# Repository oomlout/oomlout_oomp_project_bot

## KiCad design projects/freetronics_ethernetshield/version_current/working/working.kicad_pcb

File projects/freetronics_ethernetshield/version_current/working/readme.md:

# OOMP Project  
## EthernetShield  by freetronics  
  
oomp key: oomp_projects_flat_freetronics_ethernetshield  
(snippet of original readme)  
  
Freetronics Ethernet Shield  
===========================  
Copyright 2010-2012 Freetronics Pty Ltd    
Freetronics site:  www.freetronics.com    
Freetronics email: info@freetronics.com    
  
10/100base-T Ethernet shield for the Freetronics Eleven, Arduino Uno,  
and other boards compatible with the R3 header format.  
  
Includes significant prototyping area using the spare shield area, and  
supports Power-over-Ethernet (PoE) using either simple jumpers for DIY  
PoE or a daughter-board module for full standards-compliant PoE.  
  
Features:  
  
 * Prototyping area.  
 * 10/100Base-T connectivity.  
 * Power-over-Ethernet "PD" (powered device) support.  
 * Activity / status indicators.  
 * Reset button wired through to Arduino reset pin.  
 * Wiznet W5100 IC reset circuit.  
 * SPI bus contention fixed for W5100 IC.  
 * Parts overlay on both the top and the bottom.  

More information is available on our product page at:  
  
  http://www.freetronics.com/ethernet  
  
The "docs" folder within this repository includes a handy copy of the  
schematic in PDF format and image(s) of the pcb.  

INSTALLATION  
------------  
The design is saved as an EAGLE project. EAGLE PCB design software is  
available from www.cadsoftusa.com free for non-commercial use. To use  
this project download it and place the directory containing these files  
into the "eagle" directory on your computer. Then open EAGLE and  
navigate to Projects -> eagle -> EthernetShieldR3.  

DISTRIBUTION  
------------  
The specific terms of distribution of this project are gove  
  full source readme at [readme_src.md](readme_src.md)  
  
source repo at: [https://github.com/freetronics/EthernetShield](https://github.com/freetronics/EthernetShield)  
## Board  

## Schematic  

[schematic pdf](working_schematic.pdf)  
## Images

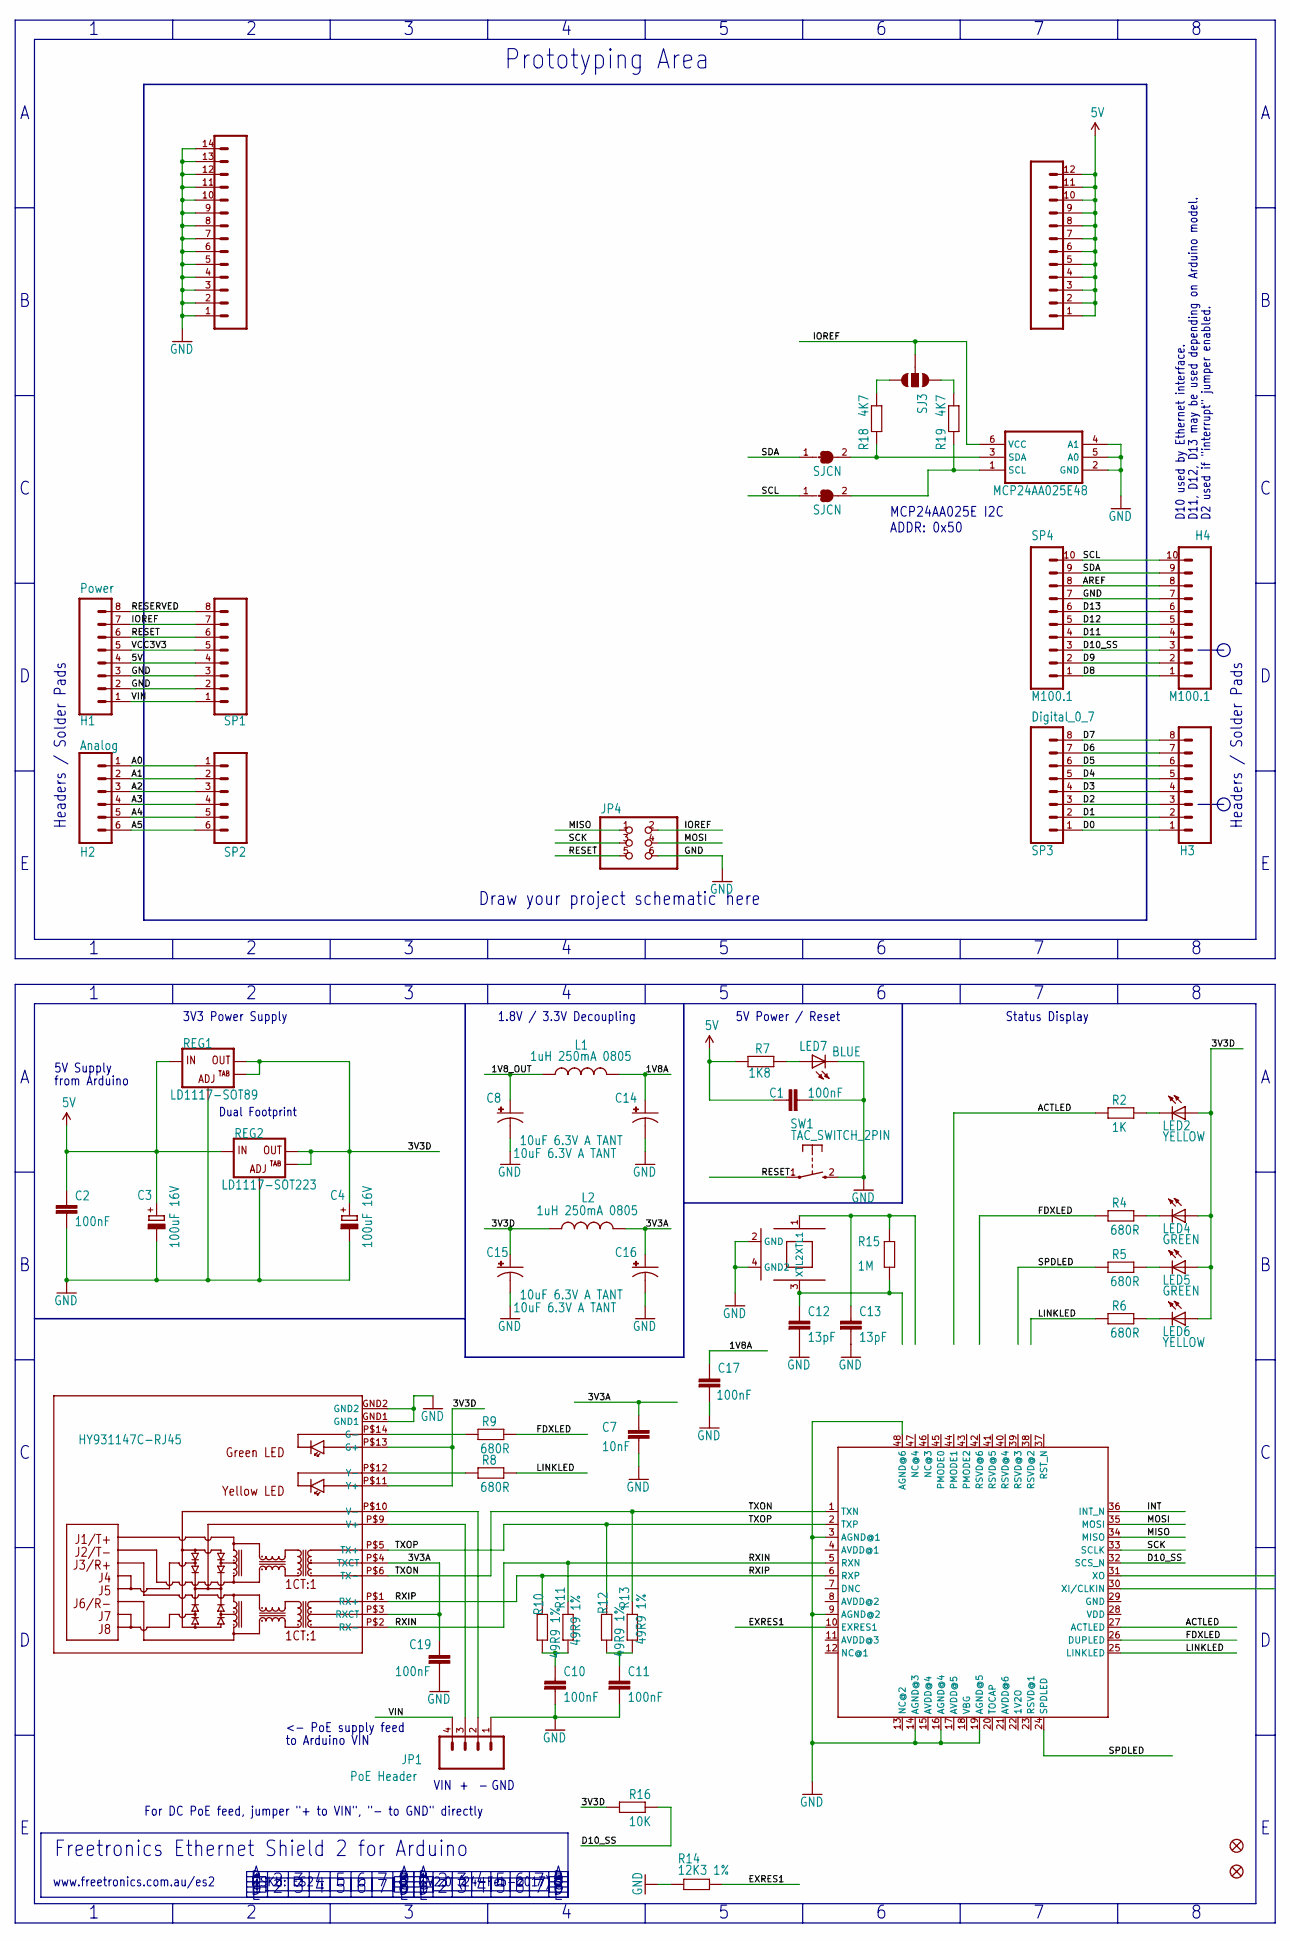
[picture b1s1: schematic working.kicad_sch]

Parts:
C1, C2, C10, C11, C17, C19: 100nF; 0603
C3, C4: 100uF 16V; PANASONIC_D
C7: 10nF; 0603
C8, C14, C15, C16: 10uF 6.3V A TANT; EIA3216
C12, C13: 13pF; 0603
H1: Power; 1X08
H2: Analog; 1X06
H3: Digital_0_7; 1X08
H4: M100.1; 1X10
IC1: W5500
IC2: MCP24AA025E48; SOT23-6
JP1: PoE Header; 1X04
JP4: PINHD-2X3; 2X03
L1, L2: 1uH 250mA 0805; L2012C
LED2, LED6: YELLOW; LED-0603
LED4, LED5: GREEN; LED-0603
LED7: BLUE; LED-0603
PADS_5V0: M12PTH; 1X12
PADS_GND0: M14; 1X14
R2: 1K; 0603
R4, R5, R6, R8, R9: 680R; 0603
R7: 1K8; 0603
R10, R11, R12, R13: 49R9 1%; 0603
R14: 12K3 1%; 0603
R15: 1M; 0603
R16: 10K; 0603
R18, R19: 4K7; 0603
REG1: LD1117-SOT89; SOT89
REG2: LD1117-SOT223; SOT223
SCK1: HY931147C-RJ45; HY931147C
SJ1, SJ2: SJCN; SJC
SJ3: SOLDERJUMPER_2WAYT; SJ_2
SP1: M08; 1X08
SP2: Analog; 1X06
SP3: Digital_0_7; 1X08
SP4: M100.1; 1X10
SW1: TAC_SWITCH_2PIN; TACTILE_SWITCH_SMD_2PIN_TINY
U$6, U$8: FIDUCIAL1X2.5; FIDUCIAL-1X2.5
XTL1: CRYSTAL-GND3X2; CRYSTAL-SMD-3X2

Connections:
1V8A: C14.A (+), C17.1, L1.2
1V8_OUT: C8.A (+), L1.1
3V3A: C7.1, C16.A (+), C19.1, L2.2, SCK1.P$3 (RXCT), SCK1.P$4 (TXCT)
3V3D: C4.+, C15.A (+), L2.1, LED2.A, LED4.A, LED5.A, LED6.A, R16.2, REG1.2 (OUT), REG1.4 (OUT@1), REG2.2 (OUT), REG2.4 (OUT@1), SCK1.P$11 (Y+), SCK1.P$13 (G+)
5V: C1.1, C2.1, C3.+, H1.4, PADS_5V0.1, PADS_5V0.2, PADS_5V0.3, PADS_5V0.4, PADS_5V0.5, PADS_5V0.6, PADS_5V0.7, PADS_5V0.8, PADS_5V0.9, PADS_5V0.10, PADS_5V0.11, PADS_5V0.12, R7.1, REG1.3 (IN), REG2.3 (IN), SP1.4
A0: H2.1, SP2.1
A1: H2.2, SP2.2
A2: H2.3, SP2.3
A3: H2.4, SP2.4
A4: H2.5, SP2.5
A5: H2.6, SP2.6
ACTLED: IC1.27 (ACTLED), R2.2
AREF: H4.8, SP4.8
D0: H3.1, SP3.1
D1: H3.2, SP3.2
D2: H3.3, SP3.3
D3: H3.4, SP3.4
D4: H3.5, SP3.5
D5: H3.6, SP3.6
D6: H3.7, SP3.7
D7: H3.8, SP3.8
D8: H4.1, SP4.1
D9: H4.2, SP4.2
D10_SS: H4.3, IC1.32 (SCS_N), R16.1, SP4.3
D11: H4.4, SP4.4
D12: H4.5, SP4.5
D13: H4.6, SP4.6
EXRES1: IC1.10 (EXRES1), R14.2
FDXLED: IC1.26 (DUPLED), R4.2, R9.1
GND: C1.2, C2.2, C3.-, C4.-, C7.2, C8.C (-), C10.2, C11.2, C12.2, C13.2, C14.C (-), C15.C (-), C16.C (-), C17.2, C19.2, H1.2, H1.3, H4.7, IC1.3 (AGND@1), IC1.9 (AGND@2), IC1.14 (AGND@3), IC1.16 (AGND@4), IC1.19 (AGND@5), IC1.48 (AGND@6), IC2.2 (GND), IC2.4 (A1), IC2.5 (A0), JP1.1, JP4.6, LED7.C, PADS_GND0.1, PADS_GND0.2, PADS_GND0.3, PADS_GND0.4, PADS_GND0.5, PADS_GND0.6, PADS_GND0.7, PADS_GND0.8, PADS_GND0.9, PADS_GND0.10, PADS_GND0.11, PADS_GND0.12, PADS_GND0.13, PADS_GND0.14, R14.1, REG1.1 (ADJ), REG2.1 (ADJ), SCK1.GND1, SCK1.GND2, SP1.2, SP1.3, SP4.7, SW1.2 (S), XTL1.2 (GND), XTL1.4 (GND2)
INT: IC1.36 (INT_N)
IOREF: H1.7, IC2.6 (VCC), JP4.2, SJ3.2, SP1.7
LINKLED: IC1.25 (LINKLED), R6.2, R8.1
MISO: IC1.34 (MISO), JP4.1
MOSI: IC1.35 (MOSI), JP4.4
unnamed: C11.1, R12.1, R13.2
unnamed: IC2.1 (SCL), R19.2, SJ2.2
unnamed: IC2.3 (SDA), R18.2, SJ1.2
unnamed: R18.1, SJ3.3
unnamed: R19.1, SJ3.1
unnamed: R9.2, SCK1.P$14 (G-)
unnamed: JP1.3, SCK1.P$9 (V+)
unnamed: JP1.2, SCK1.P$10 (V-)
unnamed: LED7.A, R7.2
unnamed: C10.1, R10.1, R11.2
unnamed: LED5.C, R5.1
unnamed: LED6.C, R6.1
unnamed: LED4.C, R4.1
unnamed: LED2.C, R2.1
unnamed: R8.2, SCK1.P$12 (Y-)
RESERVED: H1.8, SP1.8
RESET: H1.6, JP4.5, SP1.6, SW1.1
RXIN: IC1.5 (RXN), R11.1, SCK1.P$2 (RX-)
RXIP: IC1.6 (RXP), R10.2, SCK1.P$1 (RX+)
SCK: IC1.33 (SCLK), JP4.3
SCL: H4.10, SJ2.1, SP4.10
SDA: H4.9, SJ1.1, SP4.9
SPDLED: IC1.24 (SPDLED), R5.2
TXON: IC1.1 (TXN), R13.1, SCK1.P$6 (TX-)
TXOP: IC1.2 (TXP), R12.2, SCK1.P$5 (TX+)
VCC3V3: H1.5, SP1.5
VIN: H1.1, JP1.4, SP1.1
XTLN: C13.1, R15.2, XTL1.1 (XTL1)
XTLP: C12.1, R15.1, XTL1.3 (XTL2)

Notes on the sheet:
from Arduino
Headers / Solder Pads
www.freetronics.com.au/es2
MCP24AA025E I2C ADDR: 0x50
VIN
3V3 Power Supply
D2 used if "interrupt" jumper enabled.
Status Display
to Arduino VIN
5V Supply
<- PoE supply feed
For DC PoE feed, jumper "+ to VIN", "- to GND" directly
Draw your project schematic here
5V Power / Reset
Prototyping Area
1.8V / 3.3V Decoupling
SKU: ES2
V2.0 (24-Feb-2017)
D11, D12, D13 may be used depending on Arduino model.
D10 used by Ethernet interface.
Freetronics Ethernet Shield 2 for Arduino
Dual Footprint
GND

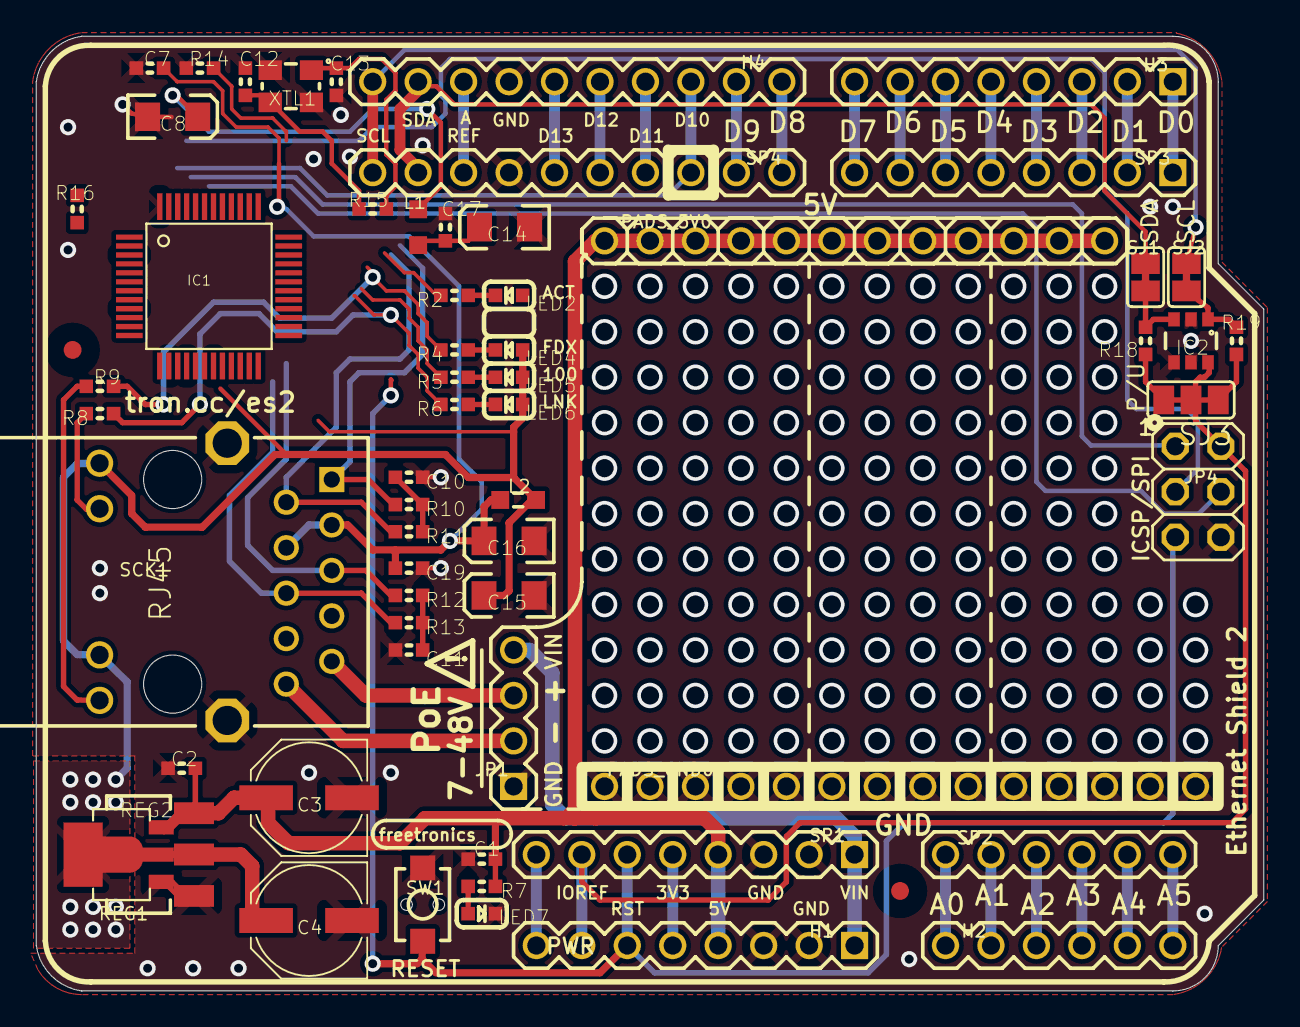
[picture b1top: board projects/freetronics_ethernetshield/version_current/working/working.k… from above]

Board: 2 copper layers, 68.6 x 53.3 mm, 62 parts (0 on the bottom side), 63 nets.

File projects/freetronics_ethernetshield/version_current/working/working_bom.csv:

"Id";"Designator";"Footprint";"Quantity";"Designation";"Supplier and ref";
1;"C2,C1,C17,C11,C19,C10";"0603";6;"100nF";;;
2;"LED7";"LED-0603";1;"BLUE";;;
3;"H1";"1X08";1;"Power";;;
4;"REG1";"SOT89";1;"LD1117-SOT89";;;
5;"SW1";"TACTILE_SWITCH_SMD_2PIN_TINY";1;"RESET";;;
6;"R19,R18";"0603";2;"4K7";;;
7;"PADS_GND0";"1X14";1;"M14";;;
8;"SP2,H2";"1X06";2;"Analog";;;
9;"XTL1";"CRYSTAL-SMD-3X2";1;"25MHZ";;;
10;"LED2,LED6";"LED-0603";2;"YELLOW";;;
11;"H4";"1X10";1;"Digital_8_13";;;
12;"PADS_5V0";"1X12";1;"M12PTH";;;
13;"R15";"0603";1;"1M";;;
14;"SP3,H3";"1X08";2;"Digital_0_7";;;
15;"R11,R13,R12,R10";"0603";4;"49R9 1%";;;
16;"R6,R8,R5,R4,R9";"0603";5;"680R";;;
17;"JP4";"2X03";1;"";;;
18;"C4,C3";"PANASONIC_D";2;"100uF 16V";;;
19;"C12,C13";"0603";2;"13pF";;;
20;"JP1";"1X04";1;"PoE Header";;;
21;"IC1";"W5500";1;"W5500";;;
22;"SJ3";"SJ_2";1;"";;;
23;"R16";"0603";1;"10K";;;
24;"C7";"0603";1;"10nF";;;
25;"U$8,U$6";"FIDUCIAL-1X2.5";2;"FIDUCIAL1X2.5";;;
26;"R2";"0603";1;"1K";;;
27;"R7";"0603";1;"1K8";;;
28;"SJ2,SJ1";"SJC";2;"";;;
29;"R14";"0603";1;"12K3 1%";;;
30;"SCK1";"HY931147C";1;"HY931147C-RJ45";;;
31;"IC2";"SOT23-6";1;"MCP24AA025E48";;;
32;"LED4,LED5";"LED-0603";2;"GREEN";;;
33;"C8,C15,C16,C14";"EIA3216";4;"10uF 6.3V A TANT";;;
34;"REG2";"SOT223";1;"LD1117-SOT223";;;
35;"SP1";"1X08";1;"";;;
36;"L2,L1";"L2012C";2;"1uH 250mA 0805";;;
37;"SP4";"1X10";1;"M100.1";;;

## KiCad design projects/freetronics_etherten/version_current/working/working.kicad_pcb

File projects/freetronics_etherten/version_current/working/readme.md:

# EtherTen by freetronics  
This is a harvested standardized copy of a project from github.  
The original project can be found at:  
https://github.com/freetronics/EtherTen  
Please consult that link for additional, details, files, and license information.  
Note: It was auto harvested and if the original repo had more than one board file or anything out of the ordinary the files here are likely not representative.

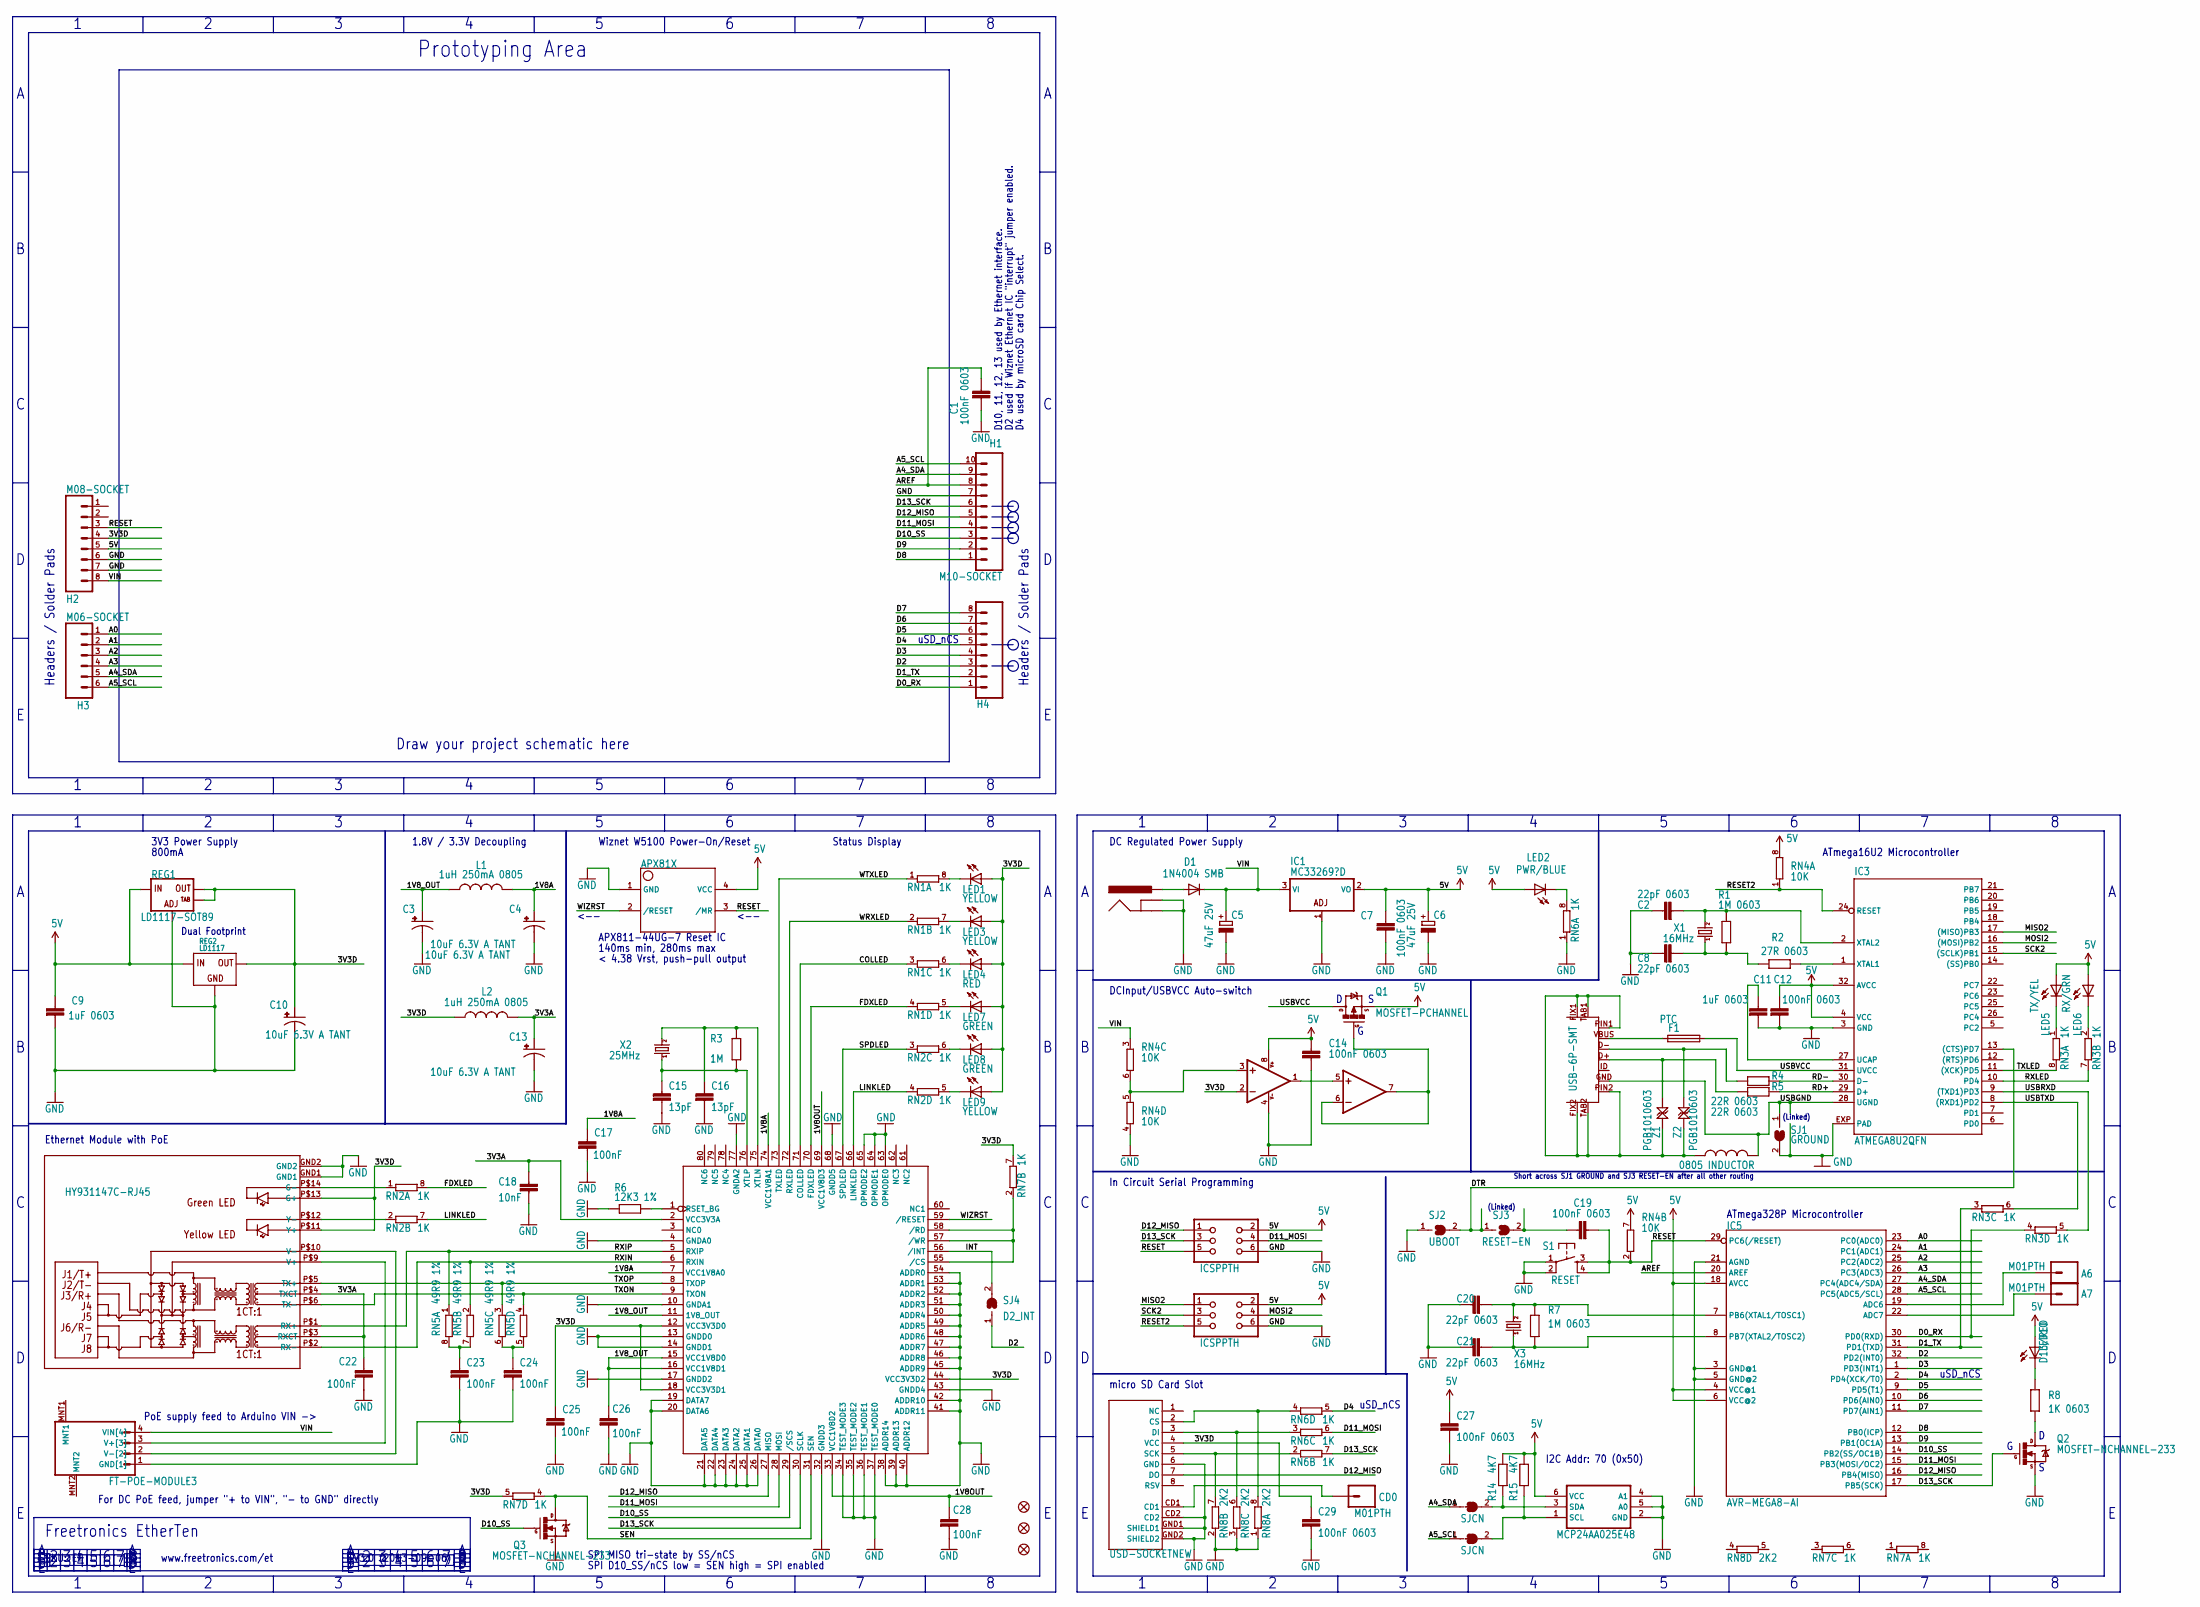
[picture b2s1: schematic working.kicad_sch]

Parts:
A6, A7: M01PTH; 1X01
C1, C7, C12, C14, C19, C27, C29: 100nF 0603; C0603
C2, C8, C20, C21: 22pF 0603; C0603
C3, C4, C10, C13: 10uF 6.3V A TANT; EIA3216
C5, C6: 47uF 25V; PANASONIC_D
C9, C11: 1uF 0603; C0603
C15, C16: 13pF; C0603
C17, C22, C23, C24, C25, C26, C28: 100nF; C0603
C18: 10nF; C0603
CD0: M01PTH; 1X01
D1: 1N4004 SMB; SMA-DIODE
F1: PTC; 1812
FID1, FID2, FID3: FIDUCIAL1X2.5; FIDUCIAL-1X2.5
H1: M10-SOCKET; 1X10-S
H2, H4: M08-SOCKET; 1X08-S
H3: M06-SOCKET; 1X06-S
IC1: MC33269?D; DPACK
IC2: APX81X; SOT143-R
IC3: ATMEGA8U2QFN; ATMEL_QFN32
IC4: LM358D; SO08
IC5: AVR-MEGA8-AI; TQFP32-08
IC6: W5100SQFP80; SQFP80
IC7: MCP24AA025E48; SOT23-6
J1: POWER_JACK-SLOTS; POWER_JACK_SLOTS
JP3: FT-POE-MODULE3; FT-POE-MODULE-NOLABEL
L1, L2: 1uH 250mA 0805; L2012C
L3: 0805 INDUCTOR; 0805-LARGE
LED1, LED3, LED9: YELLOW; LED-0603
LED2: PWR/BLUE; LED-0603
LED4: RED; LED-0603
LED5: TX/YEL; LED-0603
LED6: RX/GRN; LED-0603
LED7, LED8: GREEN; LED-0603
LED10: D13/RED; LED-0603
P1: USB-6P-SMT; USB-MICROB-MB05PMXX
P2, P3: ICSPPTH; 2X03PTH
P4: USD-SOCKETNEW; MICRO-SD-SOCKET-PP
Q1: MOSFET-PCHANNEL; SOT23
Q2, Q3: MOSFET-NCHANNEL-233; SOT23-3
R1, R7: 1M 0603; R0603
R2: 27R 0603; R0603
R3: 1M; R0603
R4, R5: 22R 0603; R0603
R6: 12K3 1%; R0603
R8: 1K 0603; R0603
R14, R15: 4K7; R0603
REG1: LD1117-SOT89; SOT89
REG2: LD1117; SOT-223
RN1, RN2, RN3, RN6, RN7: 1K; CAY16
RN4: 10K; CAY16
RN5: 49R9 1%; CAY16
RN8: 2K2; CAY16
S1: RESET; TACTILE_SMD-6MM
SJ1: GROUND; SJ
SJ2: UBOOT; SJ
SJ3: RESET-EN; SJ
SJ4: D2_INT; SJ
SJ5, SJ6: SJCN; SJC
U1: HY931147C-RJ45; HY931147C
X1, X3: 16MHz; HC49U-V
X2: 25MHz; HC49U-V
Z1, Z2: PGB1010603; TVS0603

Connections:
1V8A: C4.A (+), C17.1, IC6.7 (VCC1V8A0), IC6.74 (VCC1V8A1), L1.2
1V8OUT: C28.1, IC6.33 (VCC1V8D2), IC6.69 (VCC1V8D3)
1V8_OUT: C3.A (+), C26.1, IC6.11 (1V8_OUT), IC6.15 (VCC1V8D0), IC6.16 (VCC1V8D1), L1.1
3V3A: C13.A (+), C18.1, C22.1, IC6.2 (VCC3V3A), L2.2, U1.P$3 (RXCT), U1.P$4 (TXCT)
3V3D: C10.A (+), C25.1, C29.1, H2.4, IC4.2 (-IN), IC6.12 (VCC3V3D0), IC6.18 (VCC3V3D1), IC6.44 (VCC3V3D2), L2.1, LED1.A, LED3.A, LED4.A, LED7.A, LED8.A, LED9.A, P4.4 (VCC), REG1.2 (OUT), REG1.4 (OUT@1), REG2.2 (OUT), REG2.4 (OUT), RN7.5 (2), RN7.7 (2), U1.P$11 (Y+), U1.P$13 (G+)
5V: C6.+, C7.1, C9.1, C12.1, C14.1, C27.1, H2.5, IC1.2 (VO), IC2.4 (VCC), IC3.4 (VCC), IC3.32 (AVCC), IC4.8 (V+), IC5.4 (VCC@1), IC5.6 (VCC@2), IC5.18 (AVCC), IC7.6 (VCC), LED2.A, LED5.A, LED6.A, LED10.A, P2.2, P3.2, Q1.2 (S), R14.1, R15.1, REG1.3 (IN), REG2.3 (IN), RN4.7 (2), RN4.8 (2)
A0: H3.1, IC5.23 (PC0(ADC0))
A1: H3.2, IC5.24 (PC1(ADC1))
A2: H3.3, IC5.25 (PC2(ADC2))
A3: H3.4, IC5.26 (PC3(ADC3))
A4_SDA: H1.9, H3.5, IC5.27 (PC4(ADC4/SDA)), SJ5.1
A5_SCL: H1.10, H3.6, IC5.28 (PC5(ADC5/SCL)), SJ6.1
AREF: C1.1, H1.8, IC5.20 (AREF)
COLLED: IC6.71 (COLLED), RN1.3 (1)
D0_RX: H4.1, IC5.30 (PD0(RXD)), RN3.4 (1)
D1_TX: H4.2, IC5.31 (PD1(TXD)), RN3.3 (1)
D2: H4.3, IC5.32 (PD2(INT0)), SJ4.1
D3: H4.4, IC5.1 (PD3(INT1))
D4: H4.5, IC5.2 (PD4(XCK/T0)), RN6.5 (2)
D5: H4.6, IC5.9 (PD5(T1))
D6: H4.7, IC5.10 (PD6(AIN0))
D7: H4.8, IC5.11 (PD7(AIN1))
D8: H1.1, IC5.12 (PB0(ICP))
D9: H1.2, IC5.13 (PB1(OC1A))
D10_SS: H1.3, IC5.14 (PB2(SS/OC1B)), IC6.29 (/SCS), Q3.1 (G)
D11_MOSI: H1.4, IC5.15 (PB3(MOSI/OC2)), IC6.28 (MOSI), P2.4, RN6.6 (2)
D12_MISO: H1.5, IC5.16 (PB4(MISO)), IC6.27 (MISO), P2.1, P4.7 (DO)
D13_SCK: H1.6, IC5.17 (PB5(SCK)), IC6.30 (SCLK), P2.3, Q2.1 (G), RN6.7 (2)
DTR: IC3.13 ((CTS)PD7), SJ2.2, SJ3.1
FDXLED: IC6.70 (FDXLED), RN1.4 (1), RN2.8 (2)
GND: C1.2, C2.1, C3.C (-), C4.C (-), C5.-, C6.-, C7.2, C8.1, C9.2, C10.C (-), C11.2, C12.2, C13.C (-), C14.2, C15.2, C16.2, C17.2, C18.2, C20.1, C21.1, C22.2, C23.2, C24.2, C25.2, C26.2, C27.2, C28.2, C29.2, H1.7, H2.6, H2.7, IC1.1 (ADJ), IC2.1 (GND), IC3.3 (GND), IC3.EXP (PAD), IC4.4 (V-), IC5.3 (GND@1), IC5.5 (GND@2), IC5.21 (AGND), IC6.4 (GNDA0), IC6.10 (GNDA1), IC6.13 (GNDD0), IC6.14 (GNDD1), IC6.17 (GNDD2), IC6.19 (DATA7), IC6.20 (DATA6), IC6.21 (DATA5), IC6.22 (DATA4), IC6.23 (DATA3), IC6.24 (DATA2), IC6.25 (DATA1), IC6.26 (DATA0), IC6.32 (GNDD3), IC6.34 (TEST_MODE3), IC6.35 (TEST_MODE2), IC6.36 (TEST_MODE1), IC6.37 (TEST_MODE0), IC6.38 (ADDR14), IC6.39 (ADDR13), IC6.40 (ADDR12), IC6.41 (ADDR11), IC6.42 (ADDR10), IC6.43 (GNDD4), IC6.45 (ADDR9), IC6.46 (ADDR8), IC6.47 (ADDR7), IC6.48 (ADDR6), IC6.49 (ADDR5), IC6.50 (ADDR4), IC6.51 (ADDR3), IC6.52 (ADDR2), IC6.53 (ADDR1), IC6.54 (ADDR0), IC6.63 (OPMODE0), IC6.64 (OPMODE1), IC6.65 (OPMODE2), IC6.68 (GNDD5), IC6.77 (GNDA2), IC7.2 (GND), IC7.4 (A1), IC7.5 (A0), J1.GND, J1.GNDBREAK, JP3.1 (GND[1]), P2.6, P3.6, P4.6 (GND), P4.CD2, P4.GND1 (SHIELD1), P4.GND2 (SHIELD2), Q2.2 (S), Q3.2 (S), R6.1, REG1.1 (ADJ), REG2.1 (GND), RN4.4 (1), RN6.1, RN8.1, RN8.2 (1), RN8.3 (1), S1.1, S1.2, SJ1.2, SJ2.1, U1.GND1, U1.GND2
INT: IC6.56 (/INT), SJ4.2
LINKLED: IC6.66 (LINKLED), RN2.4 (1), RN2.7 (2)
MISO2: IC3.17 ((MISO)PB3), P3.1
MOSI2: IC3.16 ((MOSI)PB2), P3.4
unnamed: C24.1, RN5.5 (2), RN5.6 (2)
unnamed: C20.2, IC5.7 (PB6(XTAL1/TOSC1)), R7.2, X3.2
unnamed: C19.1, SJ3.2
unnamed: LED10.C, R8.2
unnamed: IC7.1 (SCL), R15.2, SJ6.2
unnamed: Q2.3 (D), R8.1
unnamed: C21.2, IC5.8 (PB7(XTAL2/TOSC2)), R7.1, X3.1
unnamed: IC3.1 (XTAL1), R2.1
unnamed: L3.1, P1.FIX1, P1.FIX2, P1.PIN1, P1.PIN2, P1.TAB1, P1.TAB2, Z1.2, Z2.2
unnamed: LED6.C, RN3.2 (1)
unnamed: IC4.3 (+IN), RN4.5 (2), RN4.6 (2)
unnamed: LED5.C, RN3.1
unnamed: LED2.C, RN6.8 (2)
unnamed: P1.D+, R5.2, Z1.1
unnamed: P1.D-, R4.2, Z2.1
unnamed: IC4.6 (-IN), IC4.7 (OUT), Q1.1 (G)
unnamed: IC4.1 (OUT), IC4.5 (+IN)
unnamed: P4.2 (CS), RN6.4 (1), RN8.8 (2)
unnamed: A7.1, IC5.22 (ADC7)
unnamed: A6.1, IC5.19 (ADC6)
unnamed: CD0.1, P4.CD1
unnamed: P4.5 (SCK), RN6.2 (1), RN8.7 (2)
unnamed: P4.3 (DI), RN6.3 (1), RN8.6 (2)
unnamed: LED8.C, RN2.6 (2)
unnamed: IC6.55 (/CS), IC6.57 (/WR), IC6.58 (/RD), RN7.2 (1)
unnamed: LED9.C, RN2.5 (2)
unnamed: IC7.3 (SDA), R14.2, SJ5.2
unnamed: D1.A, J1.PWR
unnamed: RN2.1, U1.P$14 (G-)
unnamed: JP3.3 (V+[3]), U1.P$9 (V+)
unnamed: JP3.2 (V-[2]), U1.P$10 (V-)
unnamed: C2.2, IC3.2 (XTAL2), R1.2, X1.2
unnamed: C8.2, R1.1, R2.2, X1.1
unnamed: F1.1, P1.VBUS
unnamed: C11.1, IC3.27 (UCAP)
unnamed: C23.1, RN5.7 (2), RN5.8 (2)
unnamed: IC6.1 (RSET_BG), R6.2
unnamed: LED7.C, RN1.5 (2)
unnamed: LED4.C, RN1.6 (2)
unnamed: LED3.C, RN1.7 (2)
unnamed: LED1.C, RN1.8 (2)
unnamed: RN2.2 (1), U1.P$12 (Y-)
RD+: IC3.29 (D+), R5.1
RD-: IC3.30 (D-), R4.1
RESET: C19.2, H2.3, IC2.3 (/MR), IC5.29 (PC6(/RESET)), P2.5, RN4.2 (1), S1.3, S1.4
RESET2: IC3.24 (RESET), P3.5, RN4.1
RXIN: IC6.6 (RXIN), RN5.2 (1), U1.P$2 (RX-)
RXIP: IC6.5 (RXIP), RN5.1, U1.P$1 (RX+)
RXLED: IC3.10 (PD4), RN3.7 (2)
SCK2: IC3.15 ((SCLK)PB1), P3.3
SEN: IC6.31 (SEN), Q3.3 (D), RN7.4 (1)
SPDLED: IC6.67 (SPDLED), RN2.3 (1)
TXLED: IC3.11 ((XCK)PD5), RN3.8 (2)
TXON: IC6.9 (TXON), RN5.4 (1), U1.P$6 (TX-)
TXOP: IC6.8 (TXOP), RN5.3 (1), U1.P$5 (TX+)
USBGND: IC3.28 (UGND), L3.2, P1.GND, SJ1.1
USBRXD: IC3.9 ((TXD1)PD3), RN3.5 (2)
USBTXD: IC3.8 ((RXD1)PD2), RN3.6 (2)
USBVCC: F1.2, IC3.31 (UVCC), Q1.3 (D)
VIN: C5.+, D1.C, H2.8, IC1.3 (VI), JP3.4 (VIN[4]), RN4.3 (1)
WIZRST: IC2.2 (/RESET), IC6.59 (/RESET)
WRXLED: IC6.72 (RXLED), RN1.2 (1)
WTXLED: IC6.73 (TXLED), RN1.1
XTLN: C16.1, IC6.75 (XTLN), R3.2, X2.2
XTLP: C15.1, IC6.76 (XTLP), R3.1, X2.1

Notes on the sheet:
<--
ATmega328P Microcontroller
SPI MISO tri-state by SS/nCS
Short across SJ1 GROUND and SJ3 RESET-EN after all other routing
V3.0 (2013-09-06)
Ethernet Module with PoE
uSD_nCS
ATmega16U2 Microcontroller
DC Regulated Power Supply
In Circuit Serial Programming
< 4.38 Vrst, push-pull output
D2 used if Wiznet Ethernet IC "interrupt" jumper enabled.
3V3 Power Supply
Dual Footprint
Prototyping Area
DCInput/USBVCC Auto-switch
D4 used by microSD card Chip Select.
140ms min, 280ms max
Draw your project schematic here
www.freetronics.com/et
800mA
SPI D10_SS/nCS low = SEN high = SPI enabled
Freetronics EtherTen
I2C Addr: 70 (0x50)
PoE supply feed to Arduino VIN ->
(Linked)
SKU: ET
micro SD Card Slot
D10, 11, 12, 13 used by Ethernet interface.
Headers / Solder Pads
1.8V / 3.3V Decoupling
For DC PoE feed, jumper "+ to VIN", "- to GND" directly
APX811-44UG-7 Reset IC
Wiznet W5100 Power-On/Reset
Status Display

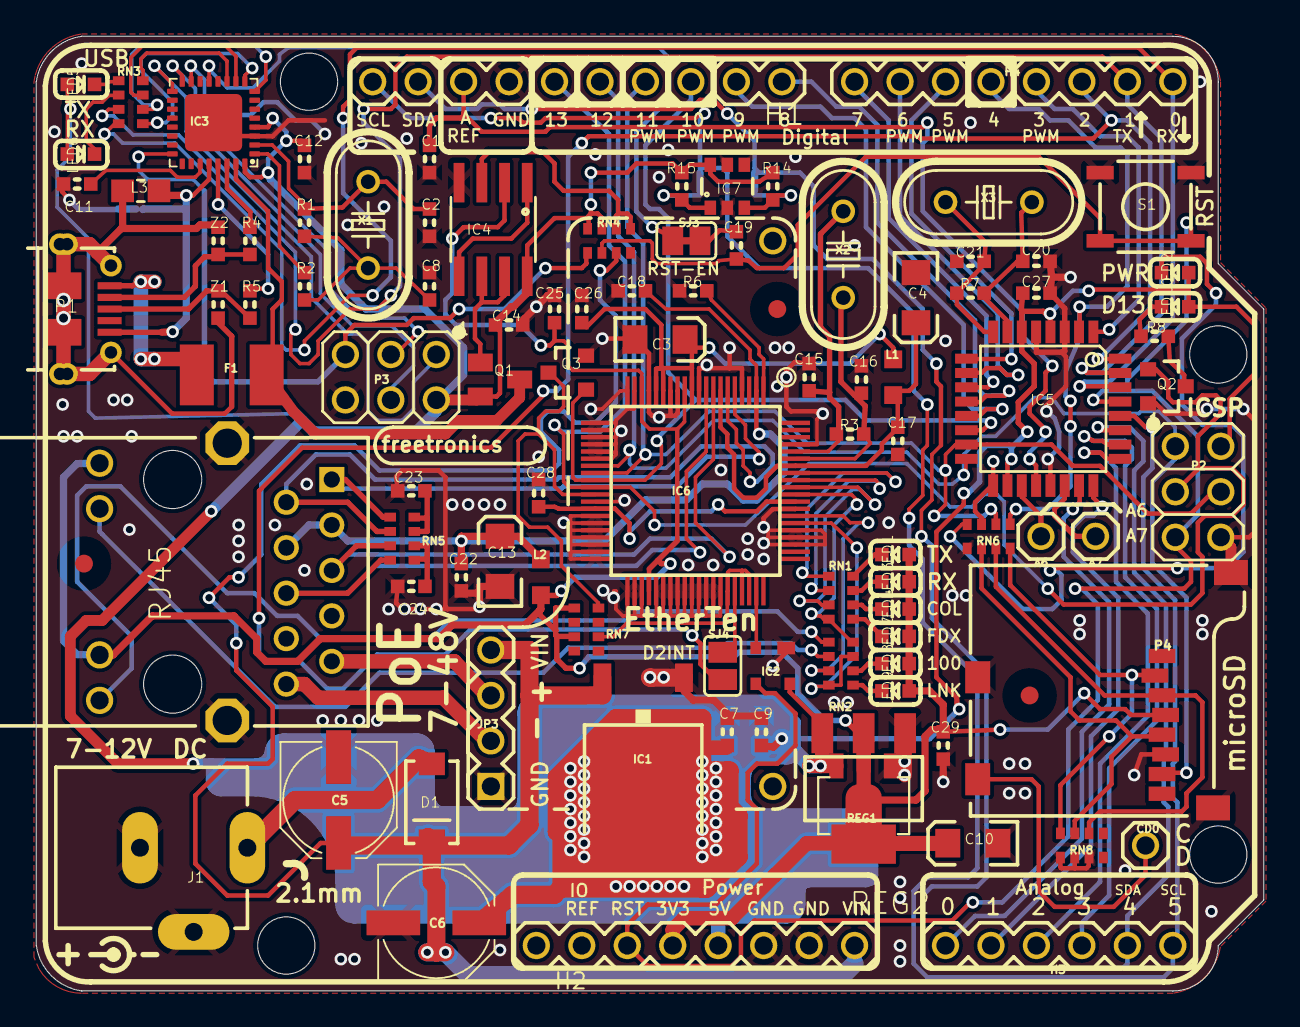
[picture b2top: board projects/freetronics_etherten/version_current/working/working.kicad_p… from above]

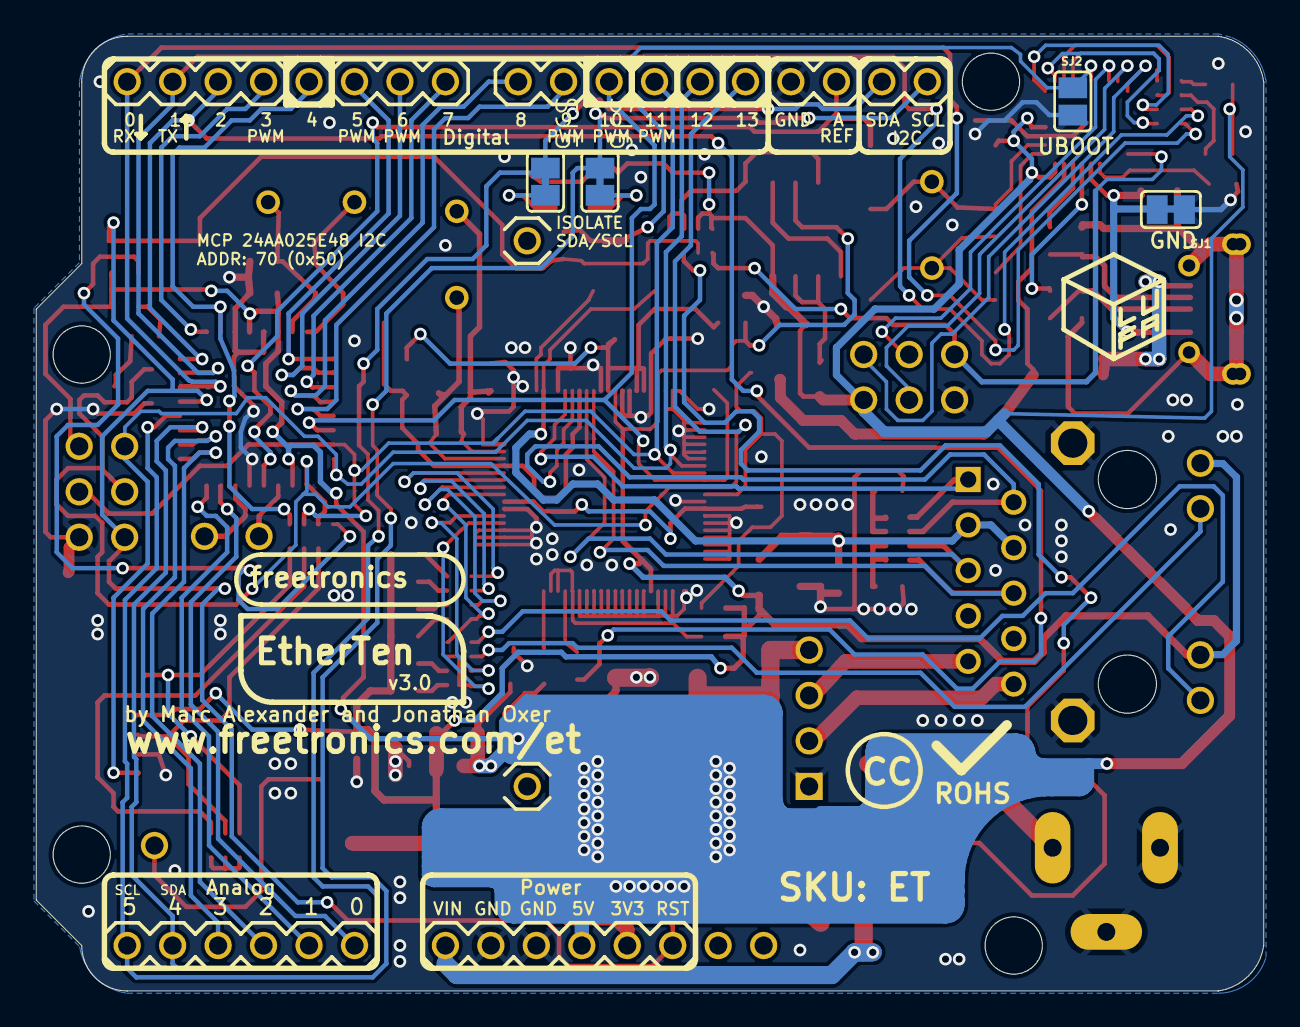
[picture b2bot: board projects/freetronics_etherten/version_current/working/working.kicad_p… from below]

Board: 2 copper layers, 68.6 x 53.3 mm, 107 parts (4 on the bottom side), 100 nets.

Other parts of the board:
@HOLE0, @HOLE1, @HOLE2, @HOLE3: (no value)

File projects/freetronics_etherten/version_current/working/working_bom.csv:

"Id";"Designator";"Footprint";"Quantity";"Designation";"Supplier and ref";
1;"C23,C25,C28,C17,C24,C26,C22";"C0603";7;"100nF";;;
2;"C8,C21,C2,C20";"C0603";4;"22pF 0603";;;
3;"C19,C12,C7,C1,C14,C29,C27";"C0603";7;"100nF 0603";;;
4;"C5,C6";"PANASONIC_D";2;"47uF 25V";;;
5;"A6,A7,CD0";"1X01";3;"M01PTH";;;
6;"J1";"POWER_JACK_SLOTS";1;"DC_2_1MM";;;
7;"X2";"HC49U-V";1;"25MHz";;;
8;"R14,R15";"R0603";2;"4K7";;;
9;"L2,L1";"L2012C";2;"1uH 250mA 0805";;;
10;"C3,C10,C13,C4";"EIA3216";4;"10uF 6.3V A TANT";;;
11;"LED5";"LED-0603";1;"TX/YEL";;;
12;"H2";"1X08-S";1;"Power";;;
13;"RN8";"CAY16";1;"2K2";;;
14;"P1";"USB-MICROB-MB05PMXX";1;"USB-6P-SMT";;;
15;"LED9,LED3,LED1";"LED-0603";3;"YELLOW";;;
16;"R3";"R0603";1;"1M";;;
17;"REG1";"SOT89";1;"LD1117-SOT89";;;
18;"S1";"TACTILE_SMD-6MM";1;"RESET";;;
19;"@HOLE1,@HOLE3,@HOLE2,@HOLE0";"";4;"";;;
20;"F1";"1812";1;"500mA PTC 1812";;;
21;"RN3,RN1,RN6,RN2,RN7";"CAY16";5;"1K";;;
22;"LED6";"LED-0603";1;"RX/GRN";;;
23;"Z1,Z2";"TVS0603";2;"PGB1010603";;;
24;"P4";"MICRO-SD-SOCKET-PP";1;"microSD";;;
25;"RN5";"CAY16";1;"49R9 1%";;;
26;"X1,X3";"HC49U-V";2;"16MHz";;;
27;"FID2,FID3,FID1";"FIDUCIAL-1X2.5";3;"FIDUCIAL1X2.5";;;
28;"LED10";"LED-0603";1;"D13/RED";;;
29;"D1";"SMA-DIODE";1;"1N4004 SMB";;;
30;"LED8,LED7";"LED-0603";2;"GREEN";;;
31;"H4";"1X08-S";1;"Digital_0_7";;;
32;"IC3";"ATMEL_QFN32";1;"ATMEGA16U2-MU";;;
33;"Q2,Q3";"SOT23-3";2;"2N7002";;;
34;"IC1";"DPACK";1;"MC33269DT-5.0";;;
35;"JP3";"FT-POE-MODULE-NOLABEL";1;"FT-POE-MODULE3";;;
36;"U1";"HY931147C";1;"HY931147C-RJ45";;;
37;"IC7";"SOT23-6";1;"MCP24AA025E48";;;
38;"SJ3";"SJ";1;"RESET-EN";;;
39;"LED4";"LED-0603";1;"RED";;;
40;"R8";"R0603";1;"1K 0603";;;
41;"C18";"C0603";1;"10nF";;;
42;"C15,C16";"C0603";2;"13pF";;;
43;"IC2";"SOT143-R";1;"APX811-44UG-7";;;
44;"IC5";"TQFP32-08";1;"ATMEGA328P TQFP32";;;
45;"REG2";"SOT-223";1;"LD1117";;;
46;"R4,R5";"R0603";2;"22R 0603";;;
47;"LED2";"LED-0603";1;"PWR/BLUE";;;
48;"L3";"0805-LARGE";1;"0805 INDUCTOR";;;
49;"H1";"1X10-S";1;"Digital_8_13";;;
50;"R6";"R0603";1;"12K3 1%";;;
51;"Q1";"SOT23";1;"FDN340P";;;
52;"C11,C9";"C0603";2;"1uF 0603";;;
53;"R1,R7";"R0603";2;"1M 0603";;;
54;"R2";"R0603";1;"27R 0603";;;
55;"H3";"1X06-S";1;"Analog";;;
56;"RN4";"CAY16";1;"10K";;;
57;"IC6";"SQFP80";1;"W5100SQFP80";;;
58;"P2";"2X03PTH";1;"ICSP:MAIN";;;
59;"SJ4";"SJ";1;"D2_INT";;;
60;"P3";"2X03PTH";1;"ICSP:USB";;;
61;"IC4";"SO08";1;"LM358D";;;
62;"SJ2";"SJ";1;"UBOOT";;;
63;"SJ1";"SJ";1;"GROUND";;;
64;"SJ6,SJ5";"SJC";2;"SJCN";;;

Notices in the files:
projects/freetronics_ethernetshield/version_current/working/working.kicad_pcb:
(c) 2014 Freetronics Pty Ltd
projects/freetronics_feedershieldmega/version_current/working/working.kicad_pcb:
Copyright 2018-2020 SuperHouse Automation
Open Hardware License:
www.tapr.org/OHL
projects/freetronics_freenfet/version_current/working/working.kicad_sch:
(C)2016 Freetronics Pty Ltd: www.freetronics.com.au
